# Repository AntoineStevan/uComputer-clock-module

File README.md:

# The clock module for the µ-C1 mother board.
This repo and project contain all the files used to create the clock module for the µ-C1 mother board.

## Table Of Content.
- [0  ](https://github.com/AntoineStevan/uComputer-clock-module/tree/main/#0-prerequisites-toc) Prerequisites.
- [1  ](https://github.com/AntoineStevan/uComputer-clock-module/tree/main/#1-some-images-toc) Some images.
- [2  ](https://github.com/AntoineStevan/uComputer-clock-module/tree/main/#2-open-in-kicad-toc) Open in KiCAD.
- [2.1](https://github.com/AntoineStevan/uComputer-clock-module/tree/main/#21-install-kicad-toc) Install KiCAD.
- [2.2](https://github.com/AntoineStevan/uComputer-clock-module/tree/main/#22-use-kicad-toc) Use KiCAD.

## 0. Prerequisites. [[toc](https://github.com/AntoineStevan/uComputer-clock-module/tree/main/#table-of-content)]
Some schematics and footprints are custom.  
One can find them [here](https://github.com/AntoineStevan/kicad-libraries).

## 1. Some images. [[toc](https://github.com/AntoineStevan/uComputer-clock-module/tree/main/#table-of-content)]
||
|:--:|
| *preview of the schematics.* |

||
|:--:|
| *preview of the pcb design (front side).* |

||
|:--:|
| *preview of the pcb design (back side).* |

## 2. Open in KiCAD. [[toc](https://github.com/AntoineStevan/uComputer-clock-module/tree/main/#table-of-content)]
This project has been designed under KiCAD, which is, according to their official website, *an open-source software tool for the creation of electronic schematic diagrams and PCB artwork.*  
All usefull official documentation can be found on the website of the Kicad software [here](https://www.kicad.org/).  
Furthermore, parts have been ordered by [Mouser](https://www.mouser.fr/) and PCBs have been manufactured by [JLCPCB](https://jlcpcb.com/).

### 2.1. Install KiCAD. [[toc](https://github.com/AntoineStevan/uComputer-clock-module/tree/main/#table-of-content)]
Official KiCAD material can be found [here](https://docs.kicad.org/5.1/en/getting_started_in_kicad/getting_started_in_kicad.html).  
Further specific material for Linux users can be found [here](https://doc.ubuntu-fr.org/kicad).

### 2.2. Use KiCAD. [[toc](https://github.com/AntoineStevan/uComputer-clock-module/tree/main/#table-of-content)]
The KiCAD team provides plenty of documentation and examples on their official website [here](https://docs.kicad.org/).  
The Internet is also full of great quality tutorials on many topics concerning KiCAD software and schematics/PCB design in general.

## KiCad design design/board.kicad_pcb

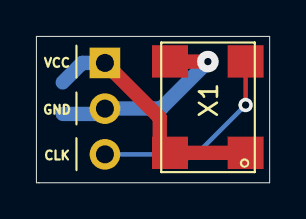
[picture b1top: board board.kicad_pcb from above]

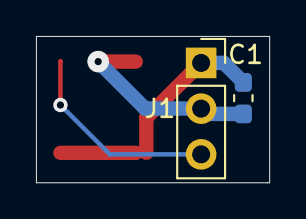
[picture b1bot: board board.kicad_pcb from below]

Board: 2 copper layers, 13.0 x 8.1 mm, 3 parts (2 on the bottom side), 3 nets.

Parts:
C1: C; C_0603_1608Metric_Pad1.05x0.95mm_HandSolder
J1: Conn_01x03_Female; PinSocket_1x03_P2.54mm_Vertical
X1: SG-8002JA; oscillator_L5.08_W4.2_PL2.0_PW1.8

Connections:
/CLK: J1.3, X1.3
GND: C1.2, J1.2, X1.2
VCC: C1.1, J1.1, X1.1, X1.4

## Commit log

2021-09-06 gitignore.
2021-09-06 Simple clock module.
2021-09-06 First PCB done.
2021-09-07 Images + README update.
2021-09-07 Name error corrected.
2021-09-07 Negative schematics + README path correction.
2021-09-11 Link to kicad-libraries + further explainations.
